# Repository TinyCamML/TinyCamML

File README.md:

# The Boron & OpenMV TinyCamML: 
### A small field-deployable camera with a cell connection.

## :scroll: Paper 
[![Earth ArXiv Preprint
DOI](https://img.shields.io/badge/%F0%9F%8C%8D%F0%9F%8C%8F%F0%9F%8C%8E%20EarthArXiv-doi.org%2F10.31223%2FX5GF20-%23FF7F2A)](https://doi.org/10.31223/X5GF20)

Farquhar, E. B., Goldstein, E. B., Bresnahan, P. J., Settin, B., Stasiewicz, J., & Anarde, K. (2026). Detection of coastal flooding with TinyCamML: A low-cost, privacy-preserving cellular-connected camera with onboard ML. Water Resources Research, 62, e2025WR042023. https://doi.org/10.1029/2025WR042023

### Overview:
Have you ever wanted to deploy a field camera, use machine learning on the images, and then send some message via cell? Us too! This repository is our work-in-progress on building the camera of our dreams. 

Our initial goal is to build cameras that overlook roadways, take pictures of the road, determine if the roadway is flooded, and send a simple message (i.e., 'flooded' or 'not flooded') via cell to a google sheet. 

The repository has multiple parts:

- a `Firmware` folder, that contains the OpenMV code and the Particle Boron code. The OpenMV handles taking pictures and using a ML model. The Boron handles publishing the ML model results to a google sheet via cell. 
- a `hardware` folder, that contains the 3D primnted parts, the circuit diagram, and the bill of materials for building the camera and the housing. 
- a `dev` folder, that has some snippets of code that were useful in building, testing, adn debugging the device
- an assets folder, that contains a [pdf of a build guide](assets/2024_12_02_BuildGuide.pdf) for the TinyCamML. If you have comments, you can add them to our [google document of the build guide](https://docs.google.com/document/d/1C9PLoJusVJ-cXYZn4gjNS5eJlwIkASh2FyWyaLo89QA/edit?usp=sharing)

### Do you want to be involved?:

- Get in touch with us, we would be happy to collaborate!
- Read through the repository to look at the files/code we provide.
-Check out the open issues and participate in our discussion.

### Code of Conduct:
We intend to foster an inclusive and respectful environment surrounding the contribution and discussion of our project. Make sure you understand our Code of Conduct.

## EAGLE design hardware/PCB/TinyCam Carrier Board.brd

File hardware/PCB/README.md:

# Directory for Carrier Board PCB.

Contains Eagle Schematic, Board Layout, CAM Data, and BoM for the PCB.

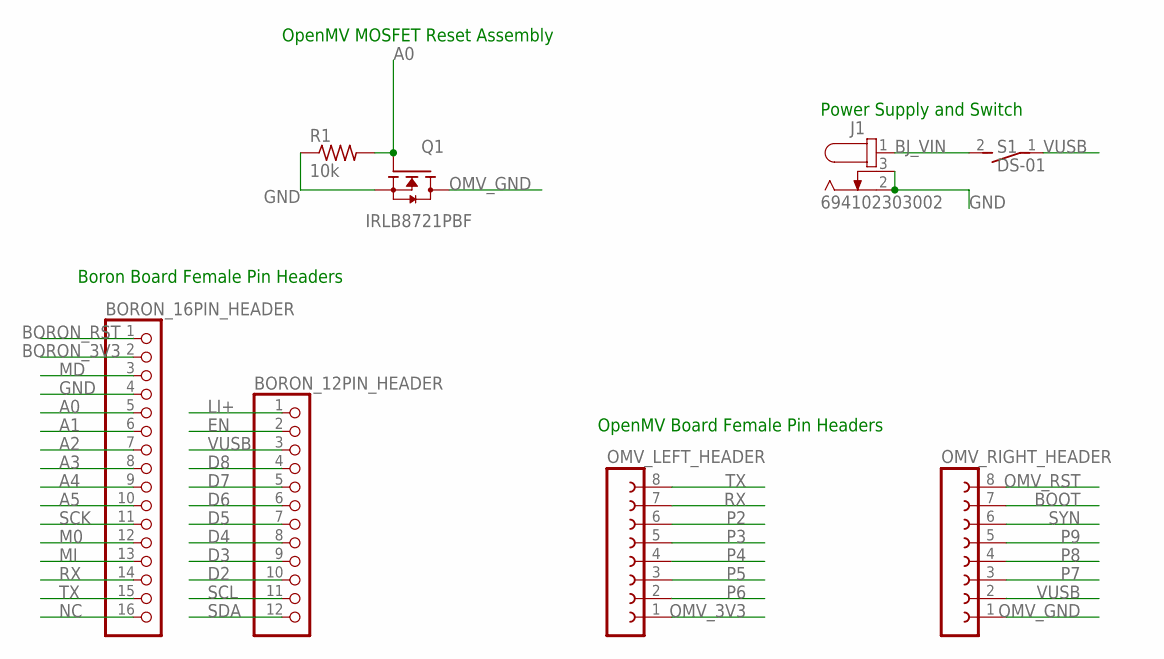
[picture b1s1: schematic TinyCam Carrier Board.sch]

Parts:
BORON_12PIN_HEADER: PINHD-1X12; 1X12
BORON_16PIN_HEADER: PINHD-1X16; 1X16
J1: 694102303002
OMV_LEFT_HEADER: FE08-1; FE08
OMV_RIGHT_HEADER: FE08-1; FE08
Q1: IRLB8721PBF; TO254P1067X483X2057-3
R1: 10k; 0204/7
S1: DS-01

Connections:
A0: BORON_16PIN_HEADER.5, Q1.1 (G), R1.2
A1: BORON_16PIN_HEADER.6
A2: BORON_16PIN_HEADER.7
A3: BORON_16PIN_HEADER.8
A4: BORON_16PIN_HEADER.9
A5: BORON_16PIN_HEADER.10
BJ_VIN: J1.1, S1.2
BOOT: OMV_RIGHT_HEADER.7
BORON_3V3: BORON_16PIN_HEADER.2
BORON_RST: BORON_16PIN_HEADER.1
D2: BORON_12PIN_HEADER.10
D3: BORON_12PIN_HEADER.9
D4: BORON_12PIN_HEADER.8
D5: BORON_12PIN_HEADER.7
D6: BORON_12PIN_HEADER.6
D7: BORON_12PIN_HEADER.5
D8: BORON_12PIN_HEADER.4
EN: BORON_12PIN_HEADER.2
GND: BORON_16PIN_HEADER.4, J1.2, J1.3, Q1.3 (S), R1.1
LI+: BORON_12PIN_HEADER.1
M0: BORON_16PIN_HEADER.12
MD: BORON_16PIN_HEADER.3
MI: BORON_16PIN_HEADER.13
NC: BORON_16PIN_HEADER.16
OMV_3V3: OMV_LEFT_HEADER.1
OMV_GND: OMV_RIGHT_HEADER.1, Q1.2 (D)
OMV_RST: OMV_RIGHT_HEADER.8
P2: OMV_LEFT_HEADER.6
P3: OMV_LEFT_HEADER.5
P4: OMV_LEFT_HEADER.4
P5: OMV_LEFT_HEADER.3
P6: OMV_LEFT_HEADER.2
P7: OMV_RIGHT_HEADER.3
P8: OMV_RIGHT_HEADER.4
P9: OMV_RIGHT_HEADER.5
RX: BORON_16PIN_HEADER.14, OMV_LEFT_HEADER.7
SCK: BORON_16PIN_HEADER.11
SCL: BORON_12PIN_HEADER.11
SDA: BORON_12PIN_HEADER.12
SYN: OMV_RIGHT_HEADER.6
TX: BORON_16PIN_HEADER.15, OMV_LEFT_HEADER.8
VUSB: BORON_12PIN_HEADER.3, OMV_RIGHT_HEADER.2, S1.1

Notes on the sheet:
Boron Board Female Pin Headers
OpenMV Board Female Pin Headers
OpenMV MOSFET Reset Assembly
Power Supply and Switch

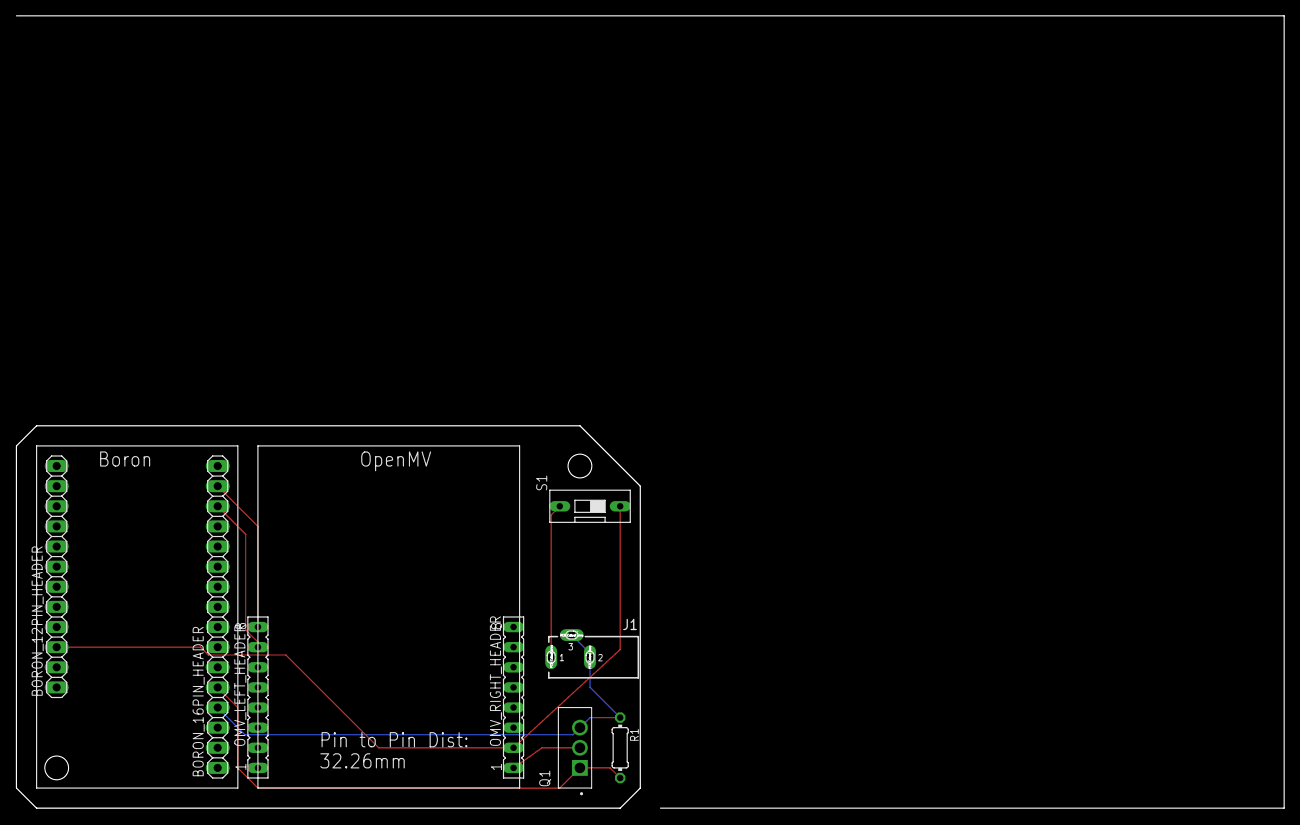
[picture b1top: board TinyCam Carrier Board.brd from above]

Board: 2 copper layers, 78.7 x 48.3 mm, 8 parts (0 on the bottom side), 7 nets.

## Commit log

2024-01-16 OpenMVCode.py
2024-01-16 MNv2Flood_cat.tflite
2024-01-18 Create PublishingCode
2024-01-18 PublishingCode.ino
2024-01-18 Update PublishingCode.ino
    PJB added comments for code improvements
2024-01-19 BoronCode.ino to Firmware/BoronCode.ino
2024-01-19 OpenMVCode.py to Firmware/OpenMVCode.py
2024-01-19 PublishingCode.ino to Firmware/PublishingCode.ino
2024-01-19 MNv2Flood_cat.tflite to Files/MNv2Flood_cat.tflite
2024-01-19 BoronAndOpenMV
2024-01-26 AddedCode
2024-01-31 NewCode
2024-01-31 beautifiedCode
2024-02-01 updatedCode
2024-02-16 updated code
2024-02-21 updatedcode
    For openMV and Boron
2024-02-21 updatedcode
    took out a hello statement hangin in there
2024-03-14 updatedVScode
2024-04-03 Rename Circuit-Diagram.png to Files/Circuit-Diagram.png
2024-04-04 Rename Circuit-Diagram.png to Circuit Diagram/Circuit-Diagram.png
2024-04-09 Adding the voltage divider firmware
2024-04-24 Getting the voltage reader to work
    removed the batteryMonitor functions and added function to read the solar panel voltage off of pin A1 on the boron. Still taking suggestions for how to calculate the percentcharge though - that isn't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
2024-04-26 Updating the code to remove voltage percentage
2024-06-04 Scaling the voltage divider back up
    Scaled it back up to be out of 5V to make the published voltage value more digestible
2024-06-12 clean up
2024-06-12 redo License
2024-06-12 Create LICENSE
2024-06-12 cleaning
2024-06-12 prevent memory growth (#14)
2024-06-12 uploaded .form file with all parts minus visor
2024-06-18 Adding improvements
2024-06-21 Added save.image and framework for the datetime
2024-06-25 Added datetime communication and file logging
    OpenMV now saves the images, receives the datetime from the Boron, and save a .txt file with datetime and flood/noflood. It takes the boron one or two cycles after connecting to cellular for everythi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
2024-07-01 Changed the voltage divider to a constant 0.00133
2024-07-11 Reorganizing
    Firmware for testing aspects of the development (e.g., voltage divider or publishing) have been moved to "Development" folder
2024-07-22 Fixed the str and filename inconsistency
2024-07-22 Update PublishOpenMV.py
    re-init the camera in the loop, to deal with sleeping... (idea from @SUPScientist 's digging in forums
2024-07-22 OpenMVFix
    Fixed openmv code and worked with Evan to clean up code
2024-07-22 switching boron code back to publish
    accidentally pushed it with cellular off - turned it back on
2024-07-22 Delete hardware/baseplate_v5.stl
    adding new baseplate design
2024-07-22 new baseplate
    updates
2024-07-22 Add files via upload
    updates
2024-07-23 Update PublishOpenMV.py
    i tried to streamline the if/else and the uart comms
2024-07-23 Update PublishOpenMV.py
    the underscore!
2024-07-23 formlabs file
2024-07-26 Delete assets/Circuit-Diagram.png
    Adding a new one
2024-07-26 Adding new circuit diagram
2024-07-30 Added the mosfet switch and function
2024-08-01 Added updated BOM
2024-08-01 Delete Firmware/OpenMV/testing_coms.py
    This was a weird interim file I had made accidentally that is not useful
2024-08-01 reorganizing the hardware folder
2024-08-02 Create readme.md for hardware folder
2024-08-06 mv 3d printed folder
2024-08-07 readme update and `dev`
2024-08-07 now with pictures
2024-08-07 more pics
2024-08-12 add simple google sheets parser
2024-08-12 update parser with met data
2024-08-12 update chart aesthetics
2024-08-20 Rename XY_bracket_v4.stl to XY_part_v4.stl
2024-08-20 Added CAD files
2024-09-05 Adding updated circuit without voltage divider
2024-09-05 Adding updated circuit without voltage divider
    Slightly better quality
2024-09-05 Commented out voltage divider code
2024-09-05 Delete copy of Development directory
    This somehow made a copy when I committed the other stuff so it's just copies of the stuff in the dev folder and not needed
2024-09-17 Most updated part
2024-09-25 new model
2024-10-09 adding brightness check
2024-10-11 changed model name
    updated it to use most recent model
2024-10-11 update model name
2024-10-17 Deleted extra curr_time definition
    The polling for curr_time was done twice so it didn't log properly. I just deleted one of them.
2024-11-07 adding daily directories
2024-11-15 changed model name
2024-11-25 Turned off boron status led
    To make it less noticeable in dark places at night
2024-12-02 Adding build guide
2024-12-02 updated BOM
2025-01-07 Create README.md
    Created directory for PCB components
2025-01-07 Added Board Eagle Files, Schematics, and BoM
2025-01-07 Updated circuit diagram image from Issue
    https://github.com/TinyCamML/TinyCamML/issues/34#issuecomment-2575946399
2025-01-07 Updated board to denote dimension units
2025-01-10 Updated PCB layout to accomodate for SD card slot
2025-01-10 Delete hardware/PCB/TinyCam Carrier Board_2025-01-07.zip
    Deleted CAM files for old PCB layout
2025-02-04 Fixed OpenMV pin distance
    Updated board layout, brd file, and CAM data with corrected 32.26mm pin to pin distance for the OpenMV H7 Plus.
2025-02-04 Delete hardware/PCB/TinyCam Carrier Board_2025-01-10.zip
    Removed CAM data for PCB with incorrect OpenMV pin distance.
2025-03-13 Updated build guide
2025-03-13 Adding build guide without PCB Board
2025-04-12 New Baseplate
2025-06-23 Updated build guide with proper baseplate
2025-06-23 BOM to include newest baseplate and the PCB board
2025-07-02 Updated BOM to exclude jumper cables for PCB vers.
2025-07-10 Updated tl library to ml
    Because of a recent firmware update to OpenMV, the previous tl.load() is no longer supported so we have to run our ml models using the ml library.
2025-07-14 older code just in case
    we shoudl retain this older code, and not overwrite it - it worked for that version of firmware
2025-08-05 Create data analysis folder
2025-08-05 Add files used to create figures in manuscript
2025-08-05 add figures produced by manuscript_figures
2025-08-05 Add script for producing figures
2025-09-19 eartharxiv badge
2025-12-19 Updated figure legend
2025-12-19 updated figure labeling
2026-01-08 change axis names
2026-03-17 add paper DOI

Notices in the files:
parts and their libraries:
Eagle_WR-DC: Copyright: Würth Elektronik
